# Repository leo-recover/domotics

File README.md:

# domotics
A simple domotics system using Raspberry-Pi, several smart nodes, and radio modules.

## WORK IN PROGRESS
Currently domotics is still WIP. This means that it's not working. Specifically:
-   HW project is OK, meaning that it can be used as a development board for this (or other) project
-   FW project is the under development, but not working
-   SW project is not started yet

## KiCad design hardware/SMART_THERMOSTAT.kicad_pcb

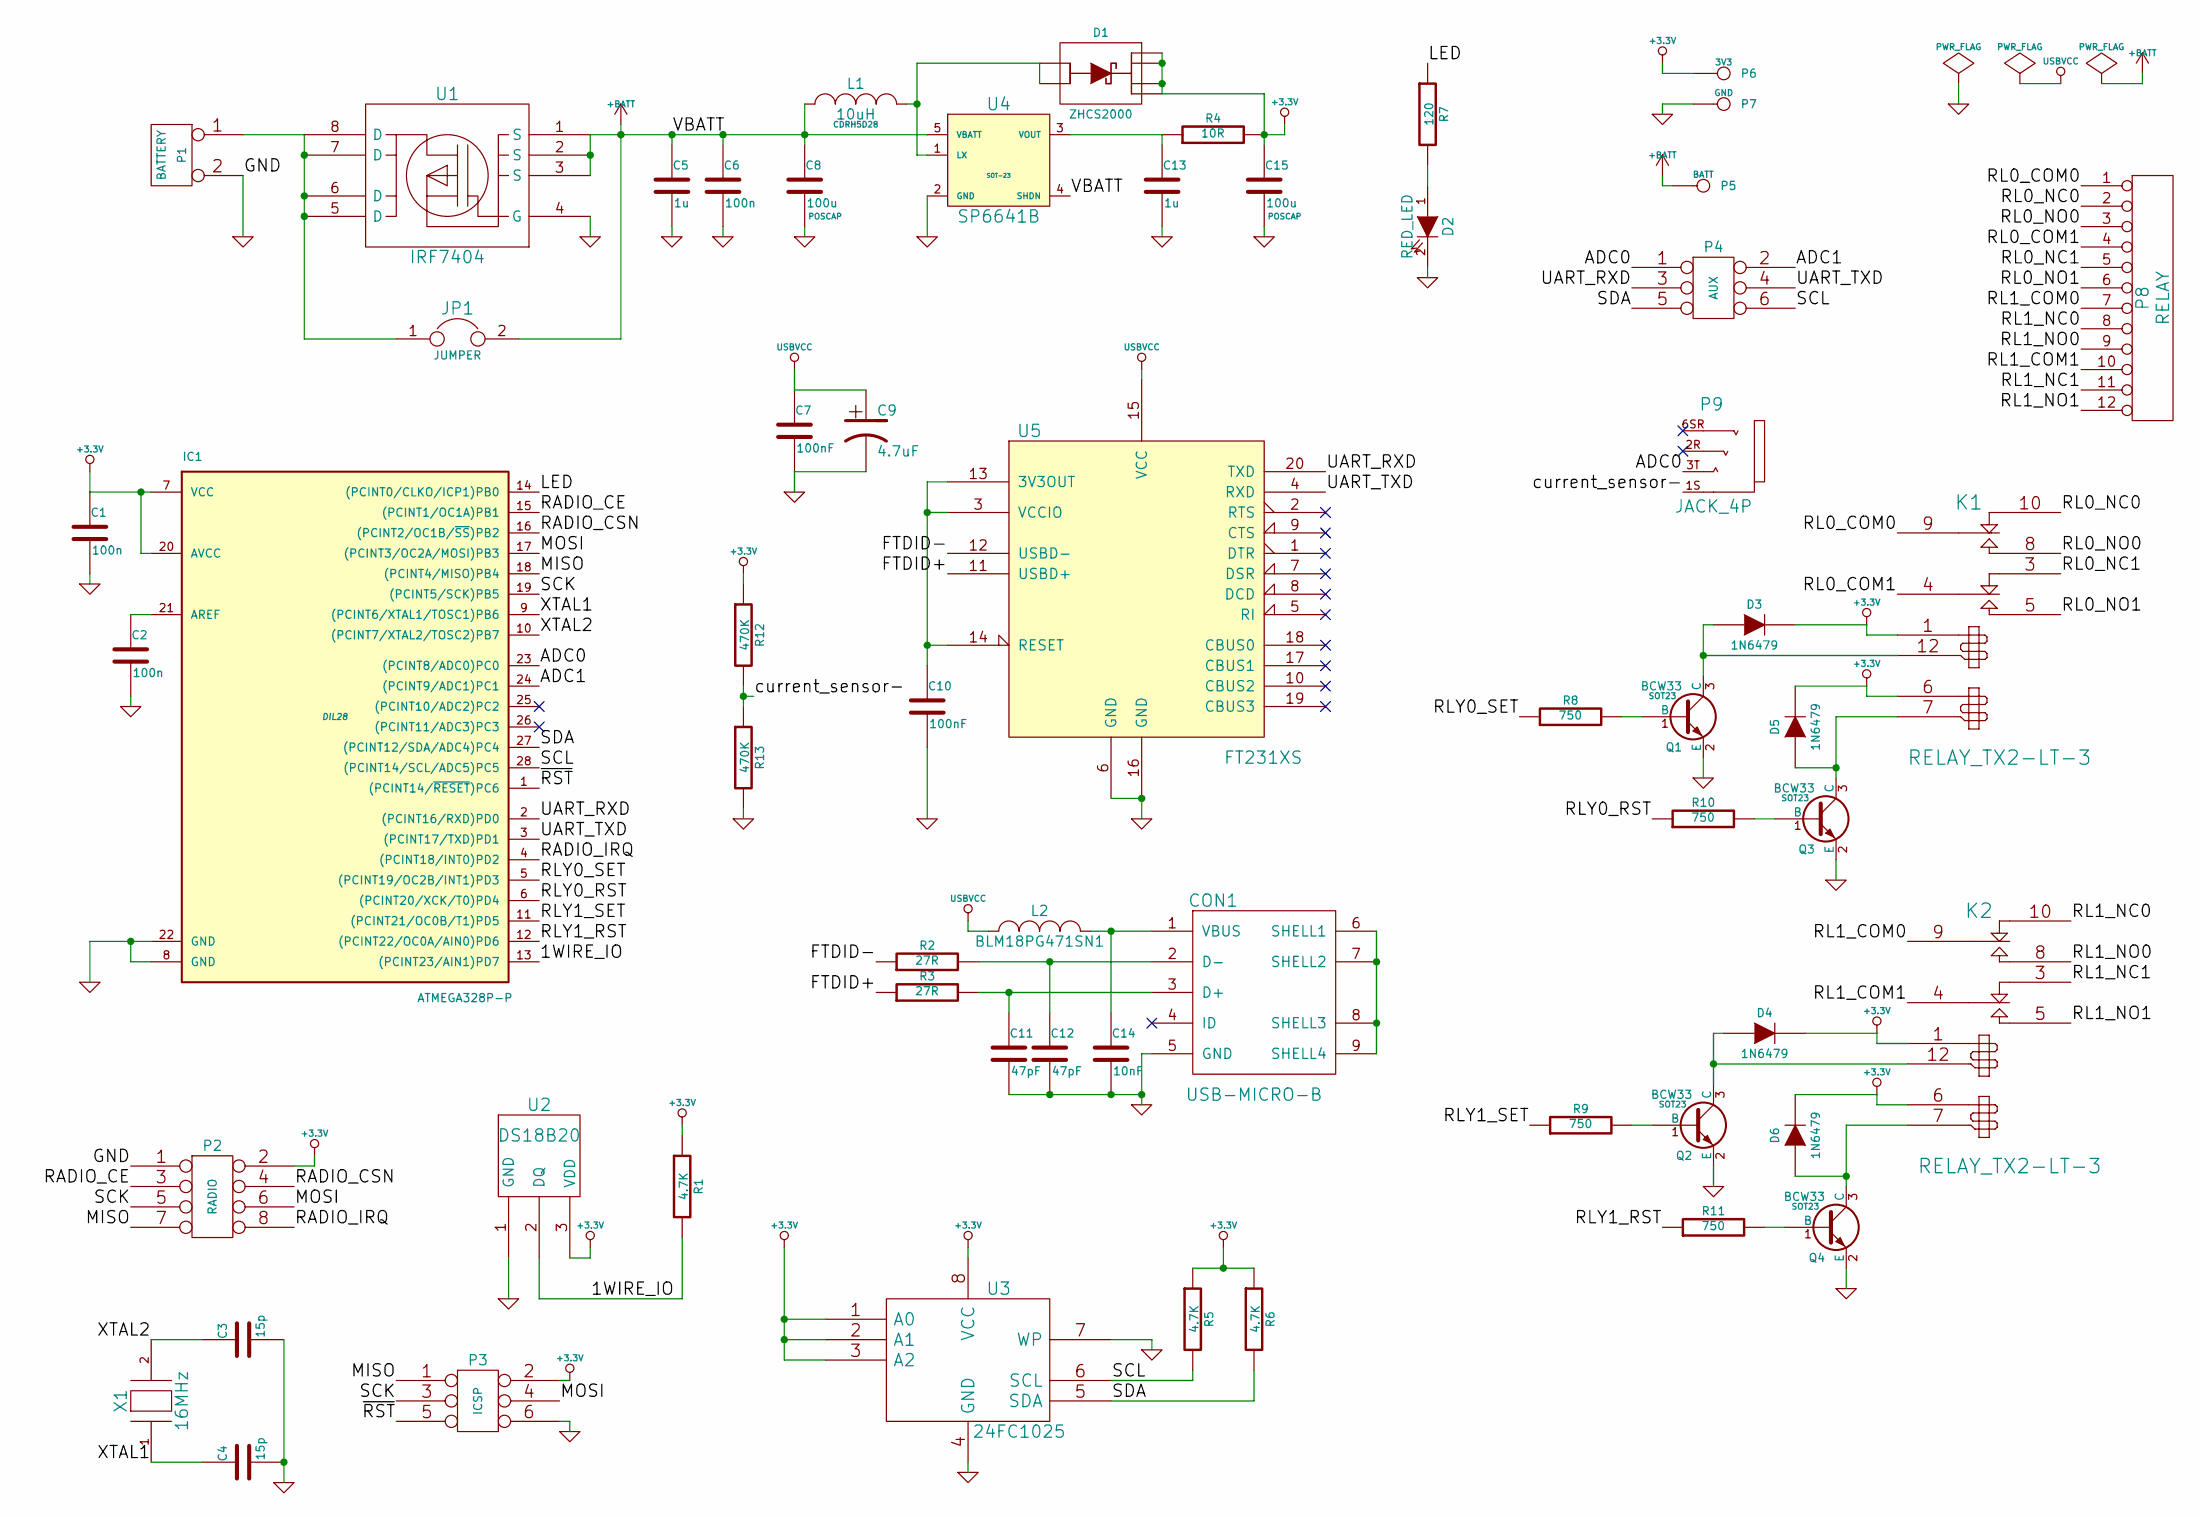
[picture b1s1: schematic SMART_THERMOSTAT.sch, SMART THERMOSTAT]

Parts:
C1, C2, C6: 100n
C3, C4: 15p
C5, C13: 1u
C7, C10: 100nF
C8, C15: 100u
C9: 4.7uF
C11, C12: 47pF
C14: 10nF
CON1: USB-MICRO-B
D1: ZHCS2000
D2: RED_LED
D3, D4, D5, D6: 1N6479
IC1: ATMEGA328P-P; DIL28
JP1: JUMPER
K1, K2: RELAY_TX2-LT-3
L1: 10uH
L2: BLM18PG471SN1
P1: BATTERY
P2: RADIO
P3: ICSP
P4: AUX
P5: BATT
P6: 3V3
P7: GND
P8: RELAY
P9: JACK_4P
Q1, Q2, Q3, Q4: BCW33; SOT23
R1, R5, R6: 4.7K
R2, R3: 27R
R4: 10R
R7: 120
R8, R9, R10, R11: 750
R12, R13: 470K
U1: IRF7404
U2: DS18B20
U3: 24FC1025
U4: SP6641B; SOT-23
U5: FT231XS
X1: 16MHz

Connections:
+3.3V: C1.1, C15.1, D1.1 (K), D1.2 (K), D1.5 (K), D1.6 (K), D3.2 (K), D4.2 (K), D5.2 (K), D6.2 (K), IC1.7 (VCC), IC1.20 (AVCC), K1.1, K1.6, K2.1, K2.6, P2.2, P3.2, P6.1, R1.1, R4.2, R5.1, R6.1, R12.1, U2.3 (VDD), U3.1 (A0), U3.2 (A1), U3.3 (A2), U3.8 (VCC)
+BATT: C5.1, C6.1, C8.1, JP1.2, L1.1, P5.1, U1.1 (S), U1.2 (S), U1.3 (S), U4.4 (SHDN), U4.5 (VBATT)
/1WIRE_IO: IC1.13 ((PCINT23/AIN1)PD7), R1.2, U2.2 (DQ)
/ADC0: IC1.23 ((PCINT8/ADC0)PC0), P4.1, P9.3T
/ADC1: IC1.24 ((PCINT9/ADC1)PC1), P4.2
/FTDID+: R3.1, U5.11 (USBD+)
/FTDID-: R2.1, U5.12 (USBD-)
/LED: IC1.14 ((PCINT0/CLKO/ICP1)PB0), R7.1
/MISO: IC1.18 ((PCINT4/MISO)PB4), P2.7, P3.1
/MOSI: IC1.17 ((PCINT3/OC2A/MOSI)PB3), P2.6, P3.4
/RADIO_CE: IC1.15 ((PCINT1/OC1A)PB1), P2.3
/RADIO_CSN: IC1.16 ((PCINT2/OC1B/~SS~)PB2), P2.4
/RADIO_IRQ: IC1.4 ((PCINT18/INT0)PD2), P2.8
/RL0_COM0: K1.9 (C2), P8.1
/RL0_COM1: K1.4 (C1), P8.4
/RL0_NC0: K1.10 (R2), P8.2
/RL0_NC1: K1.3 (R1), P8.5
/RL0_NO0: K1.8 (T2), P8.3
/RL0_NO1: K1.5 (T1), P8.6
/RL1_COM0: K2.9 (C2), P8.7
/RL1_COM1: K2.4 (C1), P8.10
/RL1_NC0: K2.10 (R2), P8.8
/RL1_NC1: K2.3 (R1), P8.11
/RL1_NO0: K2.8 (T2), P8.9
/RL1_NO1: K2.5 (T1), P8.12
/RLY0_RST: IC1.6 ((PCINT20/XCK/T0)PD4), R10.1
/RLY0_SET: IC1.5 ((PCINT19/OC2B/INT1)PD3), R8.1
/RLY1_RST: IC1.12 ((PCINT22/OC0A/AIN0)PD6), R11.1
/RLY1_SET: IC1.11 ((PCINT21/OC0B/T1)PD5), R9.1
/SCK: IC1.19 ((PCINT5/SCK)PB5), P2.5, P3.3
/SCL: IC1.28 ((PCINT14/SCL/ADC5)PC5), P4.6, R5.2, U3.6 (SCL)
/SDA: IC1.27 ((PCINT12/SDA/ADC4)PC4), P4.5, R6.2, U3.5 (SDA)
/UART_RXD: IC1.2 ((PCINT16/RXD)PD0), P4.3, U5.20 (TXD)
/UART_TXD: IC1.3 ((PCINT17/TXD)PD1), P4.4, U5.4 (RXD)
/XTAL1: C4.1, IC1.9 ((PCINT6/XTAL1/TOSC1)PB6), X1.1
/XTAL2: C3.1, IC1.10 ((PCINT7/XTAL2/TOSC2)PB7), X1.2
/current_sensor-: P9.1S, R12.2, R13.1
/~RST~: IC1.1 ((PCINT14/~RESET~)PC6), P3.5
GND: C1.2, C2.2, C3.2, C4.2, C5.2, C6.2, C7.2, C8.2, C9.2, C10.2, C11.2, C12.2, C13.2, C14.2, C15.2, CON1.5 (GND), D2.2 (K), IC1.8 (GND), IC1.22 (GND), P1.2 (PM), P2.1, P3.6, P7.1, Q1.2 (E), Q2.2 (E), Q3.2 (E), Q4.2 (E), R13.2, U1.4 (G), U2.1 (GND), U3.4 (GND), U3.7 (WP), U4.2 (GND), U5.6 (GND), U5.16 (GND)
unnamed: CON1.6 (SHELL1), CON1.7 (SHELL2), CON1.8 (SHELL3), CON1.9 (SHELL4)
unnamed: D6.1 (A), K2.7, Q4.3 (C)
unnamed: D3.1 (A), K1.12, Q1.3 (C)
unnamed: D4.1 (A), K2.12, Q2.3 (C)
unnamed: C14.1, CON1.1 (VBUS), L2.2
unnamed: C11.1, CON1.3 (D+), R3.2
unnamed: C12.1, CON1.2 (D-), R2.2
unnamed: C10.1, U5.3 (VCCIO), U5.13 (3V3OUT), U5.14 (RESET)
unnamed: C2.1, IC1.21 (AREF)
unnamed: JP1.1, P1.1, U1.5 (D), U1.6 (D), U1.7 (D), U1.8 (D)
unnamed: C13.1, R4.1, U4.3 (VOUT)
unnamed: D1.3 (A), D1.4 (A), L1.2, U4.1 (LX)
unnamed: Q3.1 (B), R10.2
unnamed: D5.1 (A), K1.7, Q3.3 (C)
unnamed: Q2.1 (B), R9.2
unnamed: Q4.1 (B), R11.2
unnamed: D2.1 (A), R7.2
unnamed: Q1.1 (B), R8.2
USBVCC: C7.1, C9.1, L2.1, U5.15 (VCC)

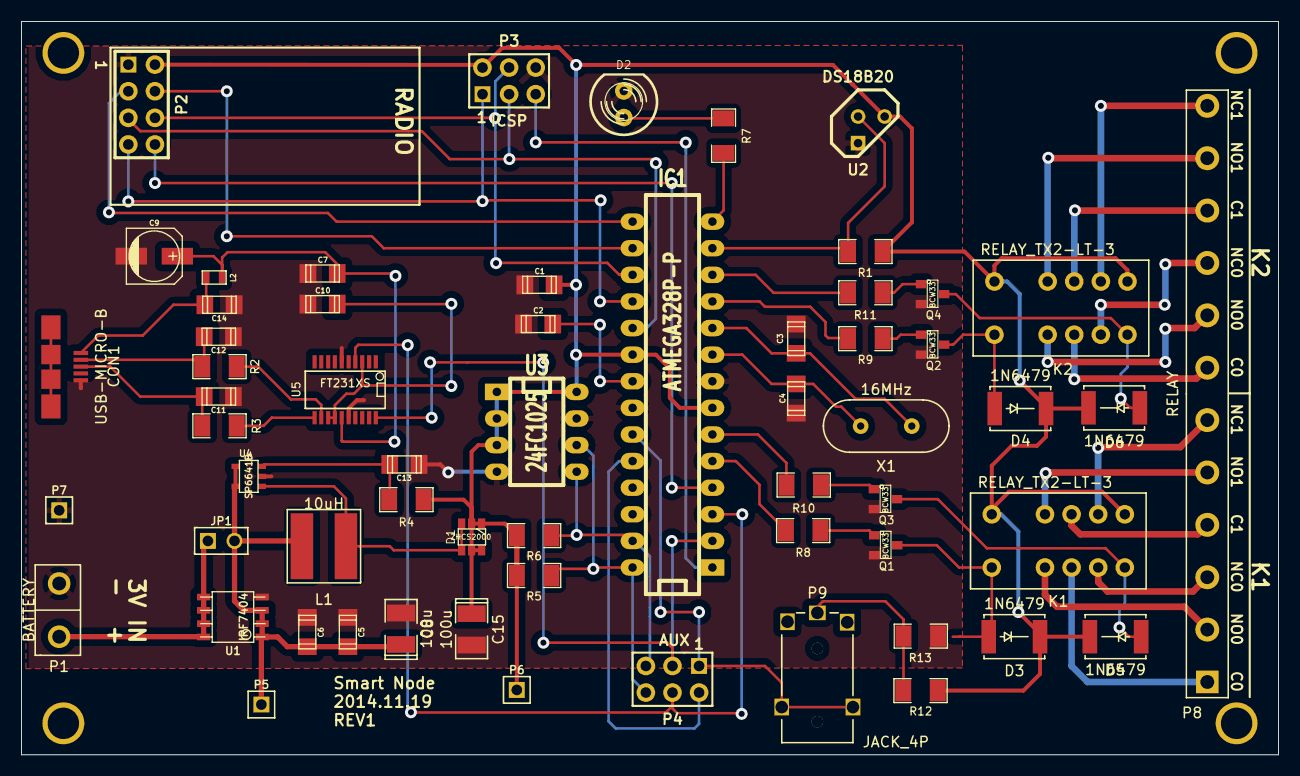
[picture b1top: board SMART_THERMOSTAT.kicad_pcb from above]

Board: 2 copper layers, 120.0 x 70.0 mm, 64 parts (0 on the bottom side), 58 nets.

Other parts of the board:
HOLE_M3, HOLE_M3#2, HOLE_M3#3, HOLE_M3#4: VAL**; HOLE_M3

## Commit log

2017-12-03 Create LICENSE
2017-12-05 Added KiCAD hardware project
2017-12-16 First version (only experimental, not working!)
2017-12-19 Renamed the modules
2017-12-19 Initial refactoring of the onewire module
2017-12-24 Onewire driver rework
    Avoid delays using the TC2 in CTC mode and a state machine
2017-12-26 Onewire driver rework
    Finished up implementation. Not tested.
2017-12-26 Minor fix
2017-12-26 TempSensor rework
    Major rewrite of the TempSensor module. Not tested!
2017-12-31 Relays module rework
    Avoid using delays but rely on a state machine
2017-12-31 General fixes
2018-01-01 Bug fixes
    Tested with simulavr for an initial debug of relays and timer modules
2018-01-02 Usage of ATOMIC_BLOCK and general refactor
2018-01-02 Initial thermostat module work
2018-01-06 Thermostat work
    Major modifications with the thermostat module. First proof of concept
    ready to be tested.
2018-01-08 UI: provide blink feature
2018-01-13 Fixed some includes
2018-01-14 Bug fixing
2018-01-14 Onewire testing
    Major refactoring due to testing. Still not working.
2018-01-14 Onewire & Temperature Sensor working
2018-01-22 Bug fix
2018-01-22 Working thermostat feature
2018-01-27 USART module rework
2018-01-27 USART transmit implementation
2018-01-27 SPI rework
2018-02-01 events module removal
2018-02-03 Minor changes to SPI
2018-02-03 Initial rework of radio driver
2018-02-04 Radio driver rework
2018-02-23 radio driver reworking
